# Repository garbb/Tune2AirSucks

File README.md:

# Tune2AirSucks
This is an attempt to create an interface between the 30pin ipod connector in my car and bluetooth so that I can stream audio from my phone. There exist several commercial products that perform this function, however none of the ones I could find supported displaying song information on my stereo.

It uses a [teensy 3.1](https://www.pjrc.com/teensy/teensy31.html) arduino-comptable board connected to a [BC127 chip] (https://www.sparkfun.com/products/12819) to manage the bluetooth connection.

It will support audio streaming over A2DP and remote control over AVRCP and also transmit song title/artist/album metadata if your phone has AVRCP 1.3 or greater.

The arduino folder contains code to be written to the Teensy with the arduino IDE.<br>
The eagle folder contains schematics and board files needed to make the PCB.<br>
The test folder contains random testing/debugging code such as "ipod.dock.sniffer" which is for sniffing the traffic between an ipod and a dock so I could figure out how it worked.

<br>
Some code/knowledge borrowed/stolen from the following:
* Arduino library for controlling ipods: https://github.com/finsprings/arduinaap<br>
* Purpletooth Jamboree (used for prototyping and used eagle files for audio circuit) https://www.sparkfun.com/products/11924
* BC127 Bluetooth chip arduino library from sparkfun: https://github.com/sparkfun/SparkFun_BC127_Bluetooth_Module_Arduino_Library/

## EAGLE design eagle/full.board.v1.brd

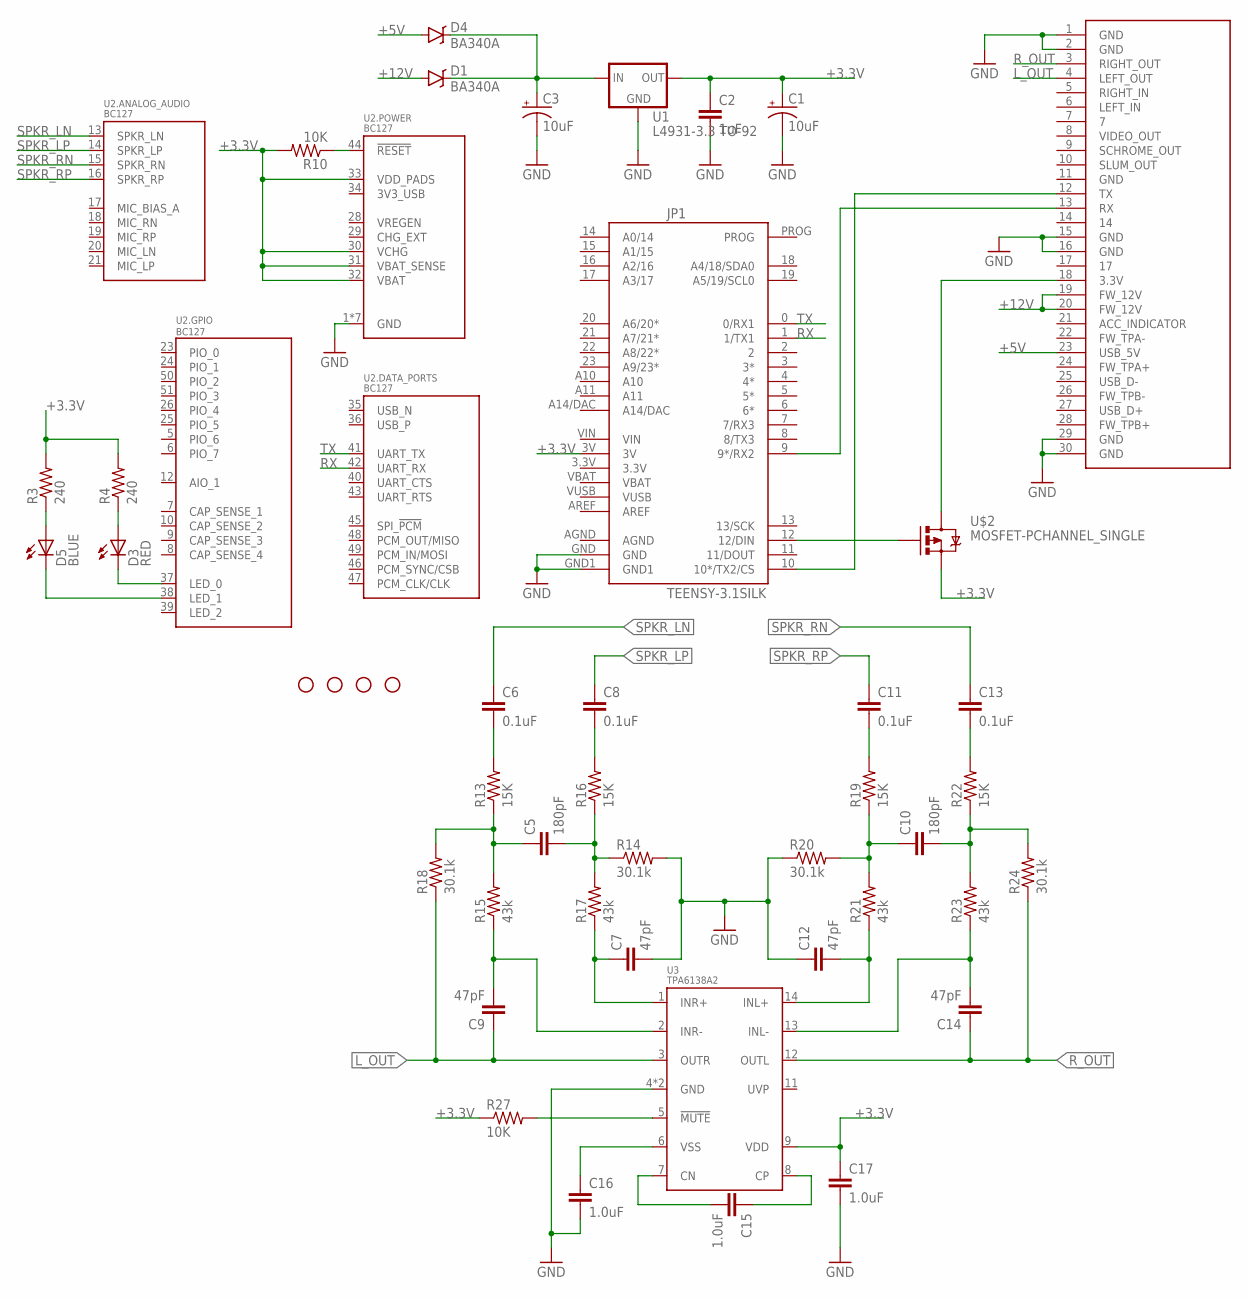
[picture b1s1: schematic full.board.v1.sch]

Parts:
C1, C3: 10uF; EIA3216
C2: 1uF; 0805
C5, C10: 180pF; 0603-CAP
C6, C8, C11, C13: 0.1uF; 0603-CAP
C7, C9, C12, C14: 47pF; 0603-CAP
C15, C16, C17: 1.0uF; 0603-CAP
D1, D4: BA340A; SMA-DIODE
D3: RED; LED-0603
D5: BLUE; LED-0603
IPOD_CONNECTOR_FEMALE: IPOD_CONNECTOR_FEMALECUTOUT; IPOD_FEM_SM_CUTOUTS
JP1: TEENSY-3.1SILK; TEENSY-3.1
R3, R4: 240; 0603-RES
R10, R27: 10K; 0603-RES
R13, R16, R19, R22: 15K; 0603-RES
R14, R18, R20, R24: 30.1k; 0603-RES
R15, R17, R21, R23: 43k; 0603-RES
STANDOFF1, STANDOFF2, STANDOFF3, STANDOFF4: STAND-OFF
U1: L4931-3.3 TO-92; TO-92
U2: BC127; BC127_XTRA_PASTE
U3: TPA6138A2; TSSOP-14
U$2: MOSFET-PCHANNEL_SINGLE; SOT563-SINGLEFET

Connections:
+3.3V: C1.A (+), C2.1, C17.1, JP1.3V, R3.2, R4.2, R10.2, R27.1, U1.1 (OUT), U2.30 (VCHG), U2.31 (VBAT_SENSE), U2.32 (VBAT), U2.33 (VDD_PADS), U3.9 (VDD), U$2.S
+5V: D4.A, IPOD_CONNECTOR_FEMALE.23 (USB_5V)
+12V: D1.A, IPOD_CONNECTOR_FEMALE.19 (FW_12V), IPOD_CONNECTOR_FEMALE.20 (FW_12V)
GND: C1.C (-), C2.2, C3.C (-), C7.2, C12.1, C16.2, C17.2, IPOD_CONNECTOR_FEMALE.1 (GND), IPOD_CONNECTOR_FEMALE.2 (GND), IPOD_CONNECTOR_FEMALE.15 (GND), IPOD_CONNECTOR_FEMALE.16 (GND), IPOD_CONNECTOR_FEMALE.29 (GND), IPOD_CONNECTOR_FEMALE.30 (GND), JP1.GND, JP1.GND1, R14.2, R20.1, U1.2 (GND), U2.1 (GND), U2.2 (GND), U2.3 (GND), U2.4 (GND), U2.11 (GND), U2.22 (GND), U2.27 (GND), U3.4 (GND), U3.10 (GND)
LED_0: D3.C, U2.37 (LED_0)
LED_1: D5.C, U2.38 (LED_1)
L_OUT: C9.1, IPOD_CONNECTOR_FEMALE.4 (LEFT_OUT), R18.1, U3.3 (OUTR)
unnamed: C3.A (+), D1.C, D4.C, U1.3 (IN)
unnamed: IPOD_CONNECTOR_FEMALE.13 (RX), JP1.9 (9*/RX2)
unnamed: IPOD_CONNECTOR_FEMALE.12 (TX), JP1.10 (10*/TX2/CS)
unnamed: R10.1, U2.44 (!RESET)
unnamed: C8.2, R16.2
unnamed: C6.2, R13.2
unnamed: R27.2, U3.5 (!MUTE)
unnamed: C5.1, R13.1, R15.2, R18.2
unnamed: C9.2, R15.1, U3.2 (INR-)
unnamed: JP1.12 (12/DIN), U$2.G
unnamed: D5.A, R3.1
unnamed: C7.1, R17.1, U3.1 (INR+)
unnamed: C5.2, R14.1, R16.1, R17.2
unnamed: D3.A, R4.1
unnamed: IPOD_CONNECTOR_FEMALE.18 (3.3V), U$2.D1 (D), U$2.D2 (D), U$2.D3 (D), U$2.D4 (D)
unnamed: C10.1, R19.1, R20.2, R21.2
unnamed: C12.2, R21.1, U3.14 (INL+)
unnamed: C11.2, R19.2
unnamed: C10.2, R22.1, R23.2, R24.2
unnamed: C13.2, R22.2
unnamed: C14.2, R23.1, U3.13 (INL-)
unnamed: C16.1, U3.6 (VSS)
unnamed: C15.2, U3.7 (CN)
unnamed: C15.1, U3.8 (CP)
RX: JP1.1 (1/TX1), U2.42 (UART_RX)
R_OUT: C14.1, IPOD_CONNECTOR_FEMALE.3 (RIGHT_OUT), R24.1, U3.12 (OUTL)
SPKR_LN: C6.1, U2.13 (SPKR_LN)
SPKR_LP: C8.1, U2.14 (SPKR_LP)
SPKR_RN: C13.1, U2.15 (SPKR_RN)
SPKR_RP: C11.1, U2.16 (SPKR_RP)
TX: JP1.0 (0/RX1), U2.41 (UART_TX)

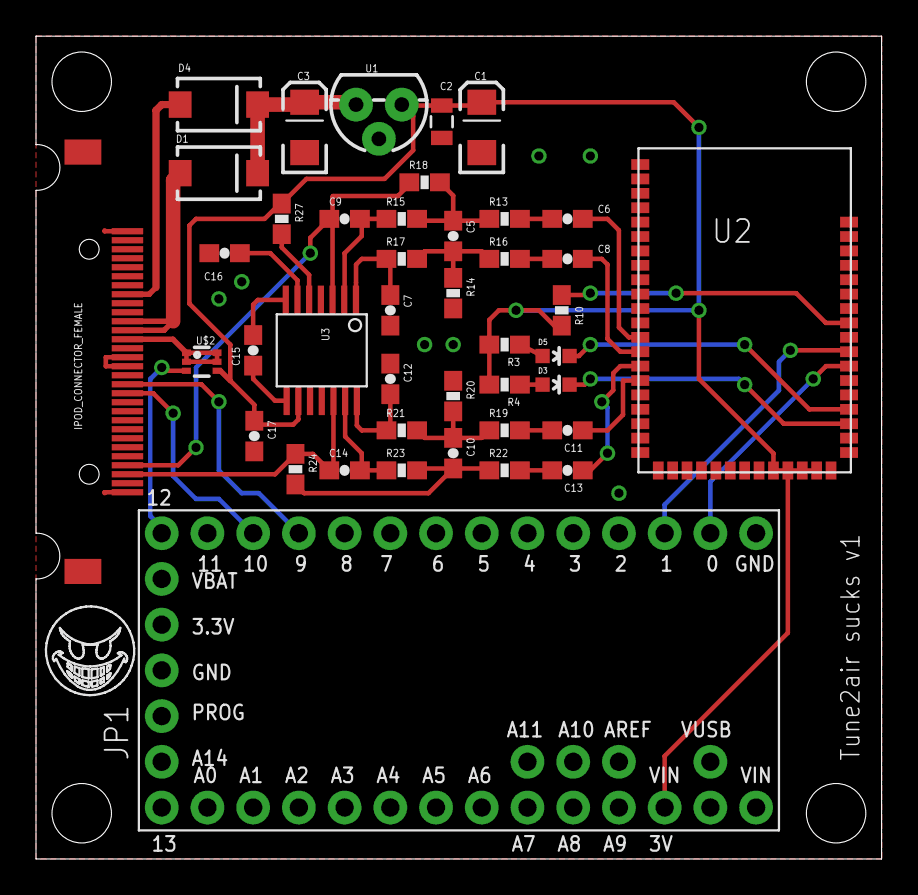
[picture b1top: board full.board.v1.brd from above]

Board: 2 copper layers, 47.0 x 45.7 mm, 47 parts (0 on the bottom side), 38 nets.

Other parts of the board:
U$1: EVIL_SMILEY_LOGO

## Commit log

2015-07-13 :boom::camel: Added .gitattributes & .gitignore files
2015-07-13 how to i github
2015-07-13 1st upload form laptop, better ipod sending debug
    1st upload form laptop
2015-07-13 TEST
2015-07-13 Revert "TEST"
    This reverts commit 343e3011adcc2c98bbd6f50aaece8a35ce61c7b3.
2015-07-13 T2A sniff log
2015-07-13 got T2A sniff logs
2015-07-13 set ad2p volume level upon connection
2015-07-13 for loop for "get names" response
2015-07-13 Revert "test"
    This reverts commit e4421d1f9886c4dbda3ccd7ac7c5a61ba87c943c.
2015-07-13 if (!send_responses) don't send polling messages
2015-07-14 test2
2015-07-14 Revert "test2"
    This reverts commit a31c845574586f82cecc38e9869e1581966728b5.
2015-07-14 Revert "Revert "test2""
    This reverts commit 5c5e6c74e5f330d5849cbfa5a3c4426c653122fe.
2015-07-14 Revert "test2"
    This reverts commit 5e6f372ce06b4db8d59d48b9de9395a066454119.
2015-07-14 Revert "Revert "test2""
    This reverts commit 35cb400991b0f243368cdfcbfe03c9fa021f9089.
2015-07-14 Revert "Revert "Revert "test2"""
    This reverts commit 1b2f9bb55bb3f4f5ff8f4745d43fff5e5671a4c5.
2015-07-14 Revert "Revert "Revert "Revert "test2""""
    This reverts commit 6f16a12b95148852ff50ca56e0bc4b693d74df6e.
2015-07-14 what
2015-07-20 wait for AVRCP connection before sending play/pause cmds
    also bug: don't set status to AVRCP_connected when getting A2DP
    connection
2015-07-20 only send accum. playtime is paused
2015-07-20 more debugging linebreaks and turn off polling spam
2015-07-21 Internalize playstate, ignore AVRCP events before connect
    Internalize playstate, ignore AVRCP events before connect
2015-07-21 state to playing upon AVRCP_TITLE (but disabled)
2015-07-21 clear out old text upon disconnect
2015-07-22 schematics
2015-07-22 don't add to accum time if aleady paused
2015-07-22 track change event resend if no text request
    resend track change event to dock if dock does not request song text
    within timeout period (currently 1sec)
2015-07-28 AVRCP reconnect to force metadata
    Implemented AVRCP reconnect when playstate changes to playing in order
    to coax stubborn devices to send metadata. Also made default text
    "Bluetooth" a constant var.
2015-07-28 metadata timeout 1000->500ms
2015-08-17 inc plist pos upon new track and 1->99 wrap
    increment playlist position upon getting new track text. Also wrap
    around playlist position to 99 if it is 1 and we --
    Also init playlist position to 1.
2015-08-17 send playlistpos - 1
2015-08-20 schematic change
2015-08-20 don't inc plistpos upon text if same as last text
2015-08-30 only reset playing time if new track
    only reset playing time if this is a new track (if title, artist, or
    album is different)
2015-08-31 only inc plistpos upon new text
    only inc playlistpos upon new text and do it when we have gotten all new
    title/artist/album text, also never decrement
2015-09-01 i spel gud
2015-09-28 dock pin18 3.3v toggle to coax mode4
2015-09-28 teensy ready
2015-09-29 perm settings comment
2015-10-01 consolidate debug input & generic vpin states
2015-10-04 swap states for 3.3v pin toggle for p-ch mosfet
    swap LOW-HIGH states for 3.3v pin toggle for p-ch mosfet
2015-10-20 3.3v mosfet pin change for pcb
2015-10-20 Folder re-org, inc. eagle files
2015-10-20 rename arduino folder
2015-10-20 remove crap, inc pic
2015-10-20 arduino IDE is dumb and requires extra folder
2015-10-21 extra BC127 codec param note
2015-10-25 max_rec=1 b/c waiting is dumb
2015-10-25 max_rec=0, even better
    tries to auto-connect only once upon boot
2015-10-27 name
2015-11-02 parse malformed status response
2015-11-10 csum in string bug and send interface v1.00
2015-11-16 no ACK for Identify, debug name changes
2015-11-17 send extra status cmd after playstate event
    send extra status cmd after playstate event is received and read
    playstate from response. This is b/c of random AVRCP_PAUSE events which
    are false?
2015-11-20 teensy power light
2015-11-24 set playstate to paused instead of stopped
    My dock will not send play command upon startup if it sees playstate as
    stopped; only if it sees playstate as paused. So if AVRCP state is ever
    stopped, set internal state to paused so that dock will send play
    command on startup.
2015-12-29 recompute text string length
    recompute text string length if leading space is added as workaround for
    checksum-in-string dock bug
2015-12-29 replace unicode apostrophe
    text from bluetooth is a unicode "RIGHT SINGLE QUOTATION MARK" instead
    of an ascii single quote/apostrophe char but my car can't handle unicode
    so let's replace it
2016-01-04 csum calc script for testing
2017-09-16 comment
2026-01-27 Update issue templates
2026-01-27 Rename bug report template to machineType 400 Issue

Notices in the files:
parts and their libraries:
SparkFun-Capacitors: Licensing: CC v3.0 Share-Alike You are welcome to use this library for commercial purposes.
SparkFun-Boards: Licensing: Creative Commons ShareAlike 4.0 International - https://creativecommons.org/licenses/by-sa/4.0
